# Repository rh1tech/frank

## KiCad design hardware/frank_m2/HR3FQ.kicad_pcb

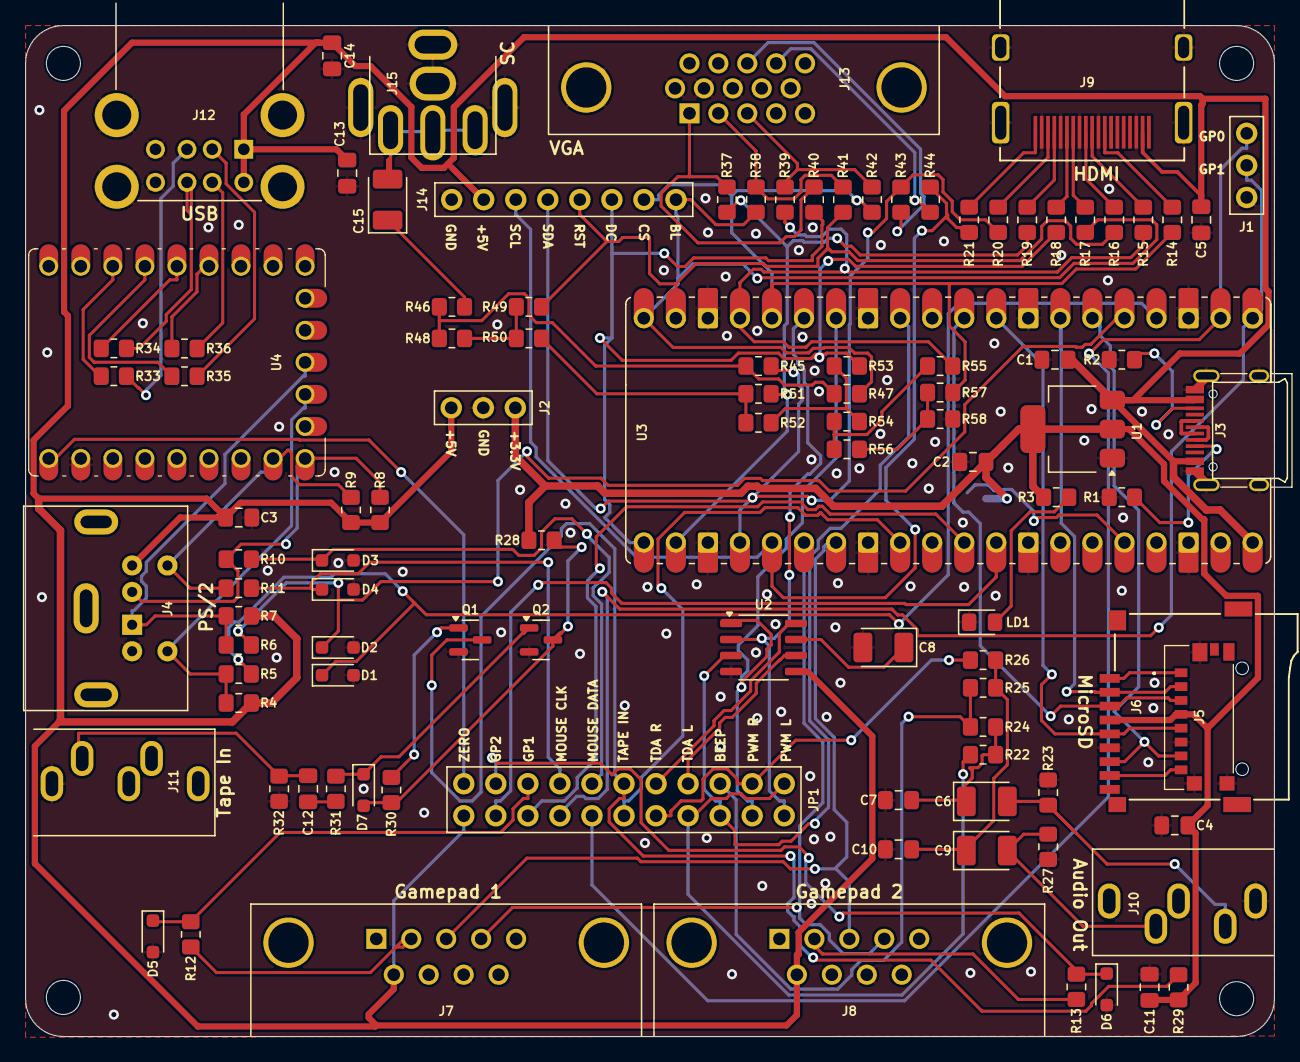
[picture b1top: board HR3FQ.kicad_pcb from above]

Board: 2 copper layers, 99.0 x 80.1 mm, 108 parts (1 on the bottom side), 91 nets.

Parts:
C1, C2, C13, C14: 10u; Capacitor (0805)
C3, C4, C5, C11, C12: 100n; Capacitor (0805)
C6, C8, C9: 10u; Capacitor (3528, tantalum, polar)
C7, C10: 10n; Capacitor (0805)
C15: 220u; Capacitor (3528, tantalum, polar)
D1, D2, D3, D4, D5, D6: 3V3; Diode (SOD-323)
D7: 1N4148; Diode (SOD-323)
H1, H2, H3, H4: Hole 2.7mm; Mounting Hole (2.7mm)
J1, J2: Pin Header 1x03; Pin Header (1x03)
J3: USB4215; USB Type C
J4: MDC-036; MiniDIN (6 Pin, female)
J5: 0475710001; MicroSD (SMD, short)
J6: 104031-0811; MicroSD (SMD, long)
J7, J8: D-SUB 9 Male; D-SUB (9 pin, male, top mount)
J9: DC3RX19JA2; HDMI (female)
J10, J11: SJ1-353XNG; Jack (3.5mm)
J12: SS-52100-004; USB Type A (stacked)
J13: D-SUB 15 Female; D-SUB (15 pin, female)
J14: Pin Header 1x08; Pin Header (1x08)
J15: RCA-103; RCA
JP1: Pin Header 2x18; Pin Header (2x11)
JP2: Jumper (Solder); Jumper (solder)
LD1: Green; LED (0805)
Q1, Q2: BC850; SOT-23
R1, R2: 5.1K; Resistor (0805)
R3, R4, R7, R8, R9, R12, R13, R22, R26, R29, R40, R41, R42: 1K; Resistor (0805)
R5, R6, R10, R11, R32, R43, R44: 100R; Resistor (0805)
R14, R15, R16, R17, R18, R19, R20, R21, R47, R49, R51, R53, R55, R57: 270R; Resistor (0805)
R23, R27, R37, R38, R39: 330R; Resistor (0805)
R24, R25: 2K; Resistor (0805)
R28, R30, R31: 10K; Resistor (0805)
R33, R34, R35, R36: 22R; Resistor (0805)
R45: 750R; Resistor (0805)
R46: 51R; Resistor (0805)
R48, R50, R52, R54, R56: 150R; Resistor (0805)
R58: 300R; Resistor (0805)
U1: NCP1117 3.3; SOT-223
U2: TDA1387T; SO-8
U3: Rasberry Pi Pico; Raspberry Pi Pico
U4: RP2040-Zero; Raspberry Pi Zero

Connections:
+3V3: C2.1, C4.2, C11.1, J2.1, J5.P4 (VDD), J6.4 (VDD), JP2.2 (B), R3.2, R28.1, R29.1, U1.2 (VO)
/A_OUTB: JP1.5, R24.2, R25.2
/A_OUTL: JP1.1, JP1.8, R22.2
/A_OUTR: JP1.3, JP1.10, R26.2
/A_TDAL: JP1.7, U2.6 (A_LEFT)
/A_TDAR: JP1.9, U2.8 (A_RIGHT)
/Audio Out/L: C6.2, J10.T, R23.1
/Audio Out/R: C9.2, J10.R, R27.1
/Composite/CVBS: C15.2, J15.1
/GP1_DATA: D5.1 (K), JP1.17, R12.1
/GP2_DATA: D6.1 (K), JP1.19, R13.1
/GPIO0: J1.2, JP1.16, U3.1 (GPIO0)
/GPIO1: J1.3, JP1.14, U3.2 (GPIO1)
/GPIO2: D1.1 (K), R5.2, U3.4 (GPIO2)
/GPIO3: D2.1 (K), R6.2, U3.5 (GPIO3)
/GPIO4: J5.P7 (DAT0), J6.7 (DAT0), U3.6 (GPIO4)
/GPIO5: J5.P2 (CD/DAT3), J6.2 (DAT3/CD), U3.7 (GPIO5)
/GPIO6: J5.P5 (CLK), J6.5 (CLK), U3.9 (GPIO6)
/GPIO7: J5.P3 (CMD), J6.3 (CMD), U3.10 (GPIO7)
/GPIO9: JP1.6, U2.3 (DATA), U3.12 (GPIO9)
/GPIO10: JP1.4, U2.1 (SCLK), U3.14 (GPIO10)
/GPIO11: JP1.2, U2.2 (LRCK), U3.15 (GPIO11)
/GPIO12: J14.7, R14.2, R42.1, R57.1, U3.16 (GPIO12)
/GPIO13: R15.2, R39.1, R55.1, U3.17 (GPIO13)
/GPIO14: J14.5, R16.2, R41.1, R49.1, U3.19 (GPIO14)
/GPIO15: J14.8, R17.2, R38.1, R47.1, U3.20 (GPIO15)
/GPIO16: J14.6, R18.2, R40.1, R53.1, U3.21 (GPIO16)
/GPIO17: R19.2, R37.1, R51.1, U3.22 (GPIO17)
/GPIO18: J14.4, R20.2, R43.2, R45.1, U3.24 (GPIO18)
/GPIO19: J14.3, R21.2, R44.2, U3.25 (GPIO19)
/GPIO20: J7.4, J8.4, U3.26 (GPIO20)
/GPIO21: J7.3, J8.3, U3.27 (GPIO21)
/GPIO22: JP1.12, U3.29 (GPIO22)
/GPIO26: JP1.18, U3.31 (GPIO26_ADC0)
/GPIO27: JP1.20, U3.32 (GPIO27_ADC1)
/KB_CLK: J4.5, R4.2, R5.1, U4.13 (12)
/KB_DATA: J4.1, R6.1, R7.2, U4.12 (11)
/LOAD_IN_D: JP1.11, Q1.3 (C), R29.2
/MS_CLK: J4.6, R9.2, R11.1, U4.16 (15)
/MS_CLK_3V: D4.1 (K), JP1.15, R11.2
/MS_DATA: J4.2, R8.2, R10.1, U4.15 (14)
/MS_DATA_3V: D3.1 (K), JP1.13, R10.2
/Micro SD/DAT1: J5.P8 (DAT1), J6.8 (DAT1)
/Micro SD/DAT2: J5.P1 (DAT2), J6.1 (DAT2)
/Power/D+: J3.6 (DP1), J3.8 (DP2)
/Power/D-: J3.5 (DN2), J3.7 (DN1)
/USB_D1M: R35.1, U4.4 (3)
/USB_D1P: R33.1, U4.3 (2)
/USB_D2M: R36.1, U4.6 (5)
/USB_D2P: R34.1, U4.5 (4)
/ZERO_VBUS: JP1.21, U4.23 (5V)
GND: C1.2, C2.2, C3.2, C4.1, C5.2, C7.2, C8.2, C10.2, C11.2, C13.2, C14.2, D1.2 (A), D2.2 (A), D3.2 (A), D4.2 (A), D5.2 (A), D6.2 (A), J1.1, J2.2, J3.1 (GND), J3.12 (GND), J3.13 (SHIELD), J4.3, J5.G1 (GND_1), J5.G2 (GND_2), J5.G3 (GND_3), J5.P6 (VSS), J6.6 (VSS), J7.8, J8.8, J9.2 (G_D2), J9.5 (G_D1), J9.8 (G_D0), J9.11 (G_CLK), J9.17 (G_DDC/CEC), J9.20 (SHIELD1), J9.21 (SHIELD2), J9.22 (SHIELD3), J9.23 (SHIELD4), J10.S, J11.S, J12.4 (GND1), J12.8 (GND2), J12.9 (Shield), J13.0, J13.5, J13.6, J13.7, J13.8, J13.10, J14.1, J15.2, LD1.1 (K), Q1.2 (E), Q2.2 (E), R1.1, R2.1, R23.2, R27.2, R32.2, R58.1, U1.1 (GND), U2.4 (AGND), U3.3 (GND), U3.8 (GND), U3.13 (GND), U3.18 (GND), U3.23 (GND), U3.28 (GND), U3.33 (AGND), U3.38 (GND), U4.22 (GND)
unnamed: C6.1, C7.1, R22.1, R24.1
unnamed: C9.1, C10.1, R25.1, R26.1
unnamed: C12.1, J11.T, R32.1
unnamed: C12.2, R31.1
unnamed: C15.1, R46.2
unnamed: D7.2 (A), Q2.3 (C), R28.2, R30.1
unnamed: D7.1 (K), Q2.1 (B), R31.2
unnamed: J3.4 (CC1), R1.2
unnamed: J3.10 (CC2), R2.2
unnamed: J7.2, R12.2
unnamed: J8.2, R13.2
unnamed: J9.12 (CLKN), R14.1
unnamed: J9.10 (CLKP), R15.1
unnamed: J9.9 (D0N), R16.1
unnamed: J9.7 (D0P), R17.1
unnamed: J9.6 (D1N), R18.1
unnamed: J9.4 (D1P), R19.1
unnamed: J9.3 (D2N), R20.1
unnamed: J9.1 (D2P), R21.1
unnamed: J12.3 (D1+), R33.2
unnamed: J12.2 (D1-), R35.2
unnamed: J12.7 (D2+), R34.2
unnamed: J12.6 (D2-), R36.2
unnamed: J13.1, R37.2, R40.2
unnamed: J13.2, R38.2, R41.2
unnamed: J13.3, R39.2, R42.2
unnamed: J13.13, R43.1
unnamed: J13.14, R44.1
unnamed: JP2.1 (A), U3.36 (3V3)
unnamed: LD1.2 (A), R3.1
unnamed: Q1.1 (B), R30.2
unnamed: R45.2, R46.1, R47.2, R48.2
unnamed: R48.1, R49.2, R50.2
unnamed: R50.1, R51.2, R52.2
unnamed: R52.1, R53.2, R54.2
unnamed: R54.1, R55.2, R56.2
unnamed: R56.1, R57.2, R58.2
unnamed: C8.1, U2.7 (FLT)
VBUS: C1.1, C3.1, C5.1, C13.1, C14.1, J2.3, J3.2 (VBUS), J3.11 (VBUS), J4.4, J7.6, J8.6, J9.18 (+5V), J12.1 (VBUS1), J12.5 (VBUS2), J14.2, JP1.22, R4.1, R7.1, R8.1, R9.1, U1.3 (VI), U2.5 (VA), U3.40 (VBUS)

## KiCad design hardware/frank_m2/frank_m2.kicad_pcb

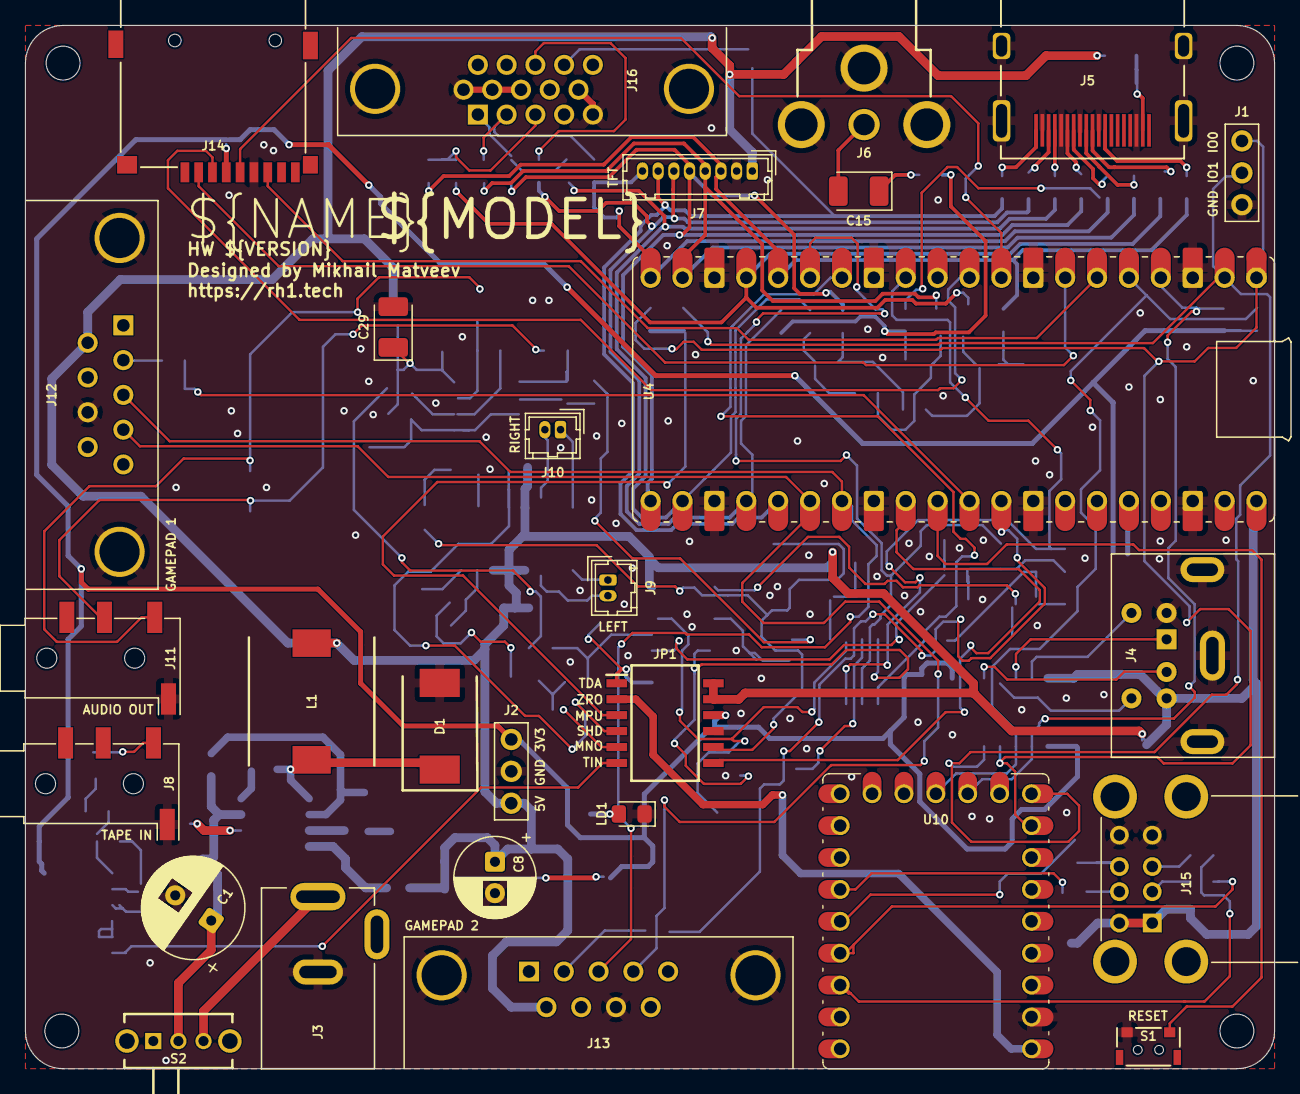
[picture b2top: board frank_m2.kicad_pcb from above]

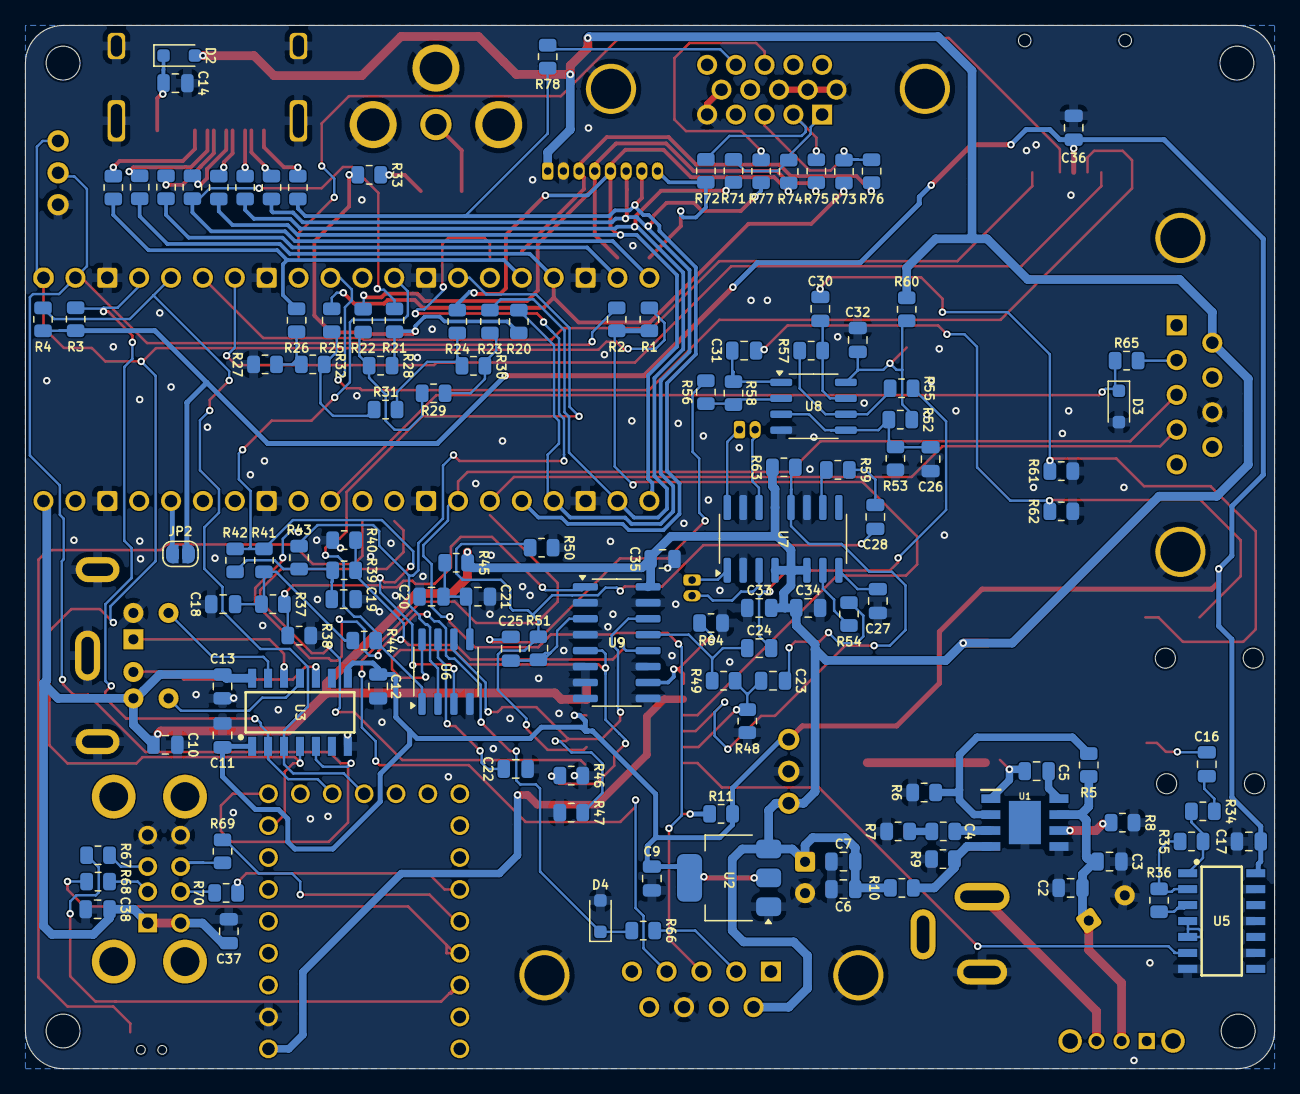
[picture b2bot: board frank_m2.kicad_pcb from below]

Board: 2 copper layers, 99.5 x 83.1 mm, 156 parts (124 on the bottom side), 117 nets.

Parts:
C1: 680u; C_Radial_D8.0mm_P3.50mm
C2, C7, C9, C20, C22, C24, C25, C26, C30, C31, C37, C38: 10u; C_0805_2012Metric
C3, C5, C6, C10, C11, C12, C13, C14, C16, C17, C21, C27, C32, C35, C36: 100n; C_0805_2012Metric
C4: 150pF; R_0805_2012Metric
C8: 220u; C_Radial_D6.3mm_P2.50mm
C15: 220u; C_3528_Tantalum
C18, C19: 47n; C_0805_2012Metric
C23, C28, C33: 1u; C_0805_2012Metric
C29: 10u; C_3528_Tantalum
C34: 47u; C_0805_2012Metric
D1: 1N5822; D_SMA_SS34
D2: 1N5819WS; D_SOD-323
D3, D4: 3V3; D_SOD-323
H1, H2, H3, H4: Hole 2.7mm; MountingHole_2.7mm
J1: UART; PinHeader_1x03_P2.54mm
J2: PWR; PinHeader_1x03_P2.54mm
J3: DC-005-5A-2.0; BarrelJack_DC-005
J4: MDC-036; MiniDIN_6pin_Female
J5: DC3RX19JA2; HDMI_Female
J6: RCA-103; BarrelJack_RCJ-012
J7: Pin Header 1x08; JST_GH_1x08_P1.25mm
J8, J11: PJ-320D; AudioJack_3.5mm_PJ320D
J9: PAM L; JST_GH_1x02_P1.25mm
J10: PAM R; JST_GH_1x02_P1.25mm
J12, J13: GP2; DSUB-9_Male_TopMount
J14: 104031-0811; MicroSD_SMD_Long
J15: SS-52100-004; USB_A_Stacked
J16: VGA; DSUB-15_Female
JP1: Config Switches; SOIC-12_P1.27mm
JP2: 3V3 Jumper; Jumper_Solder
L1: 22uH; Inductor_CDRH104RNP
LD1: Power; LED_0805
R1, R2, R3, R4, R37, R39, R49, R51, R52, R53, R54, R55, R56, R59, R63, R64: 10K; R_0805_2012Metric
R5, R7, R8, R35, R36: 100K; R_0805_2012Metric
R6: 24K; R_0805_2012Metric
R9: 8.2K; R_0805_2012Metric
R10: 43K; R_0805_2012Metric
R11, R43, R44, R65, R66, R74, R75, R76: 1K; R_0805_2012Metric
R12, R13, R14, R15, R16, R17, R18, R19, R21, R22, R23, R24, R25, R26: 270R; R_0805_2012Metric
R20: 750R; R_0805_2012Metric
R27: 300R; R_0805_2012Metric
R28, R29, R30, R31, R32: 150R; R_0805_2012Metric
R33: 51R; R_0805_2012Metric
R34: 4.7K; R_0805_2012Metric
R38, R40, R41, R42, R48, R50: 2K; R_0805_2012Metric
R45, R60, R77, R78: 100R; R_0805_2012Metric
R46, R47: 470R; R_0805_2012Metric
R57, R58: 47K; R_0805_2012Metric
R61, R62: 20K; R_0805_2012Metric
R67, R68, R69, R70: 22R; R_0805_2012Metric
R71, R72, R73: 330R; R_0805_2012Metric
S1: Reset; Button_SMD_TACT4623
S2: SK12D07VG3NS; Switch_Slide_SK12D07VG3NS
U1: MP1584EN-LF-Z; SOIC-9_P1.27mm
U2: AMS1117 3.3; SOT-223
U3: TXS0104EDR; SOIC-14_P1.27mm
U4: Rasberry Pi Pico 1/2; RaspberryPi_Pico
U5: CD4069UBM; SOIC-14_P1.27mm
U6: TDA1387T; SO-8
U7: PAM8403D; SOP-16_P1.27mm
U8: LM358; SO-8
U9: 74HC4052D; SOP-16_P1.27mm
U10: RP2040-Zero; RaspberryPi_Zero

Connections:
+3V3: C9.1, C11.1, C12.1, C17.1, C36.2, J2.1, J14.4 (VDD), JP1.10, JP2.2 (B), R3.2, R4.2, R11.2, U2.2 (VO), U3.1 (VCCA), U3.8 (OE), U5.14 (VDD)
/AMP_L: C24.1, R49.1, U9.13 (1Z)
/AMP_R: C25.1, R51.1, U9.3 (2Z)
/AUDIOSW: JP1.1, R64.2, U9.10 (S0)
/Audio/AMP_OUTL: C30.2, J11.T, R61.2
/Audio/AMP_OUTR: C31.2, J11.R, R62.2
/Audio/AMP_PAM_OUTL_M: J9.2, U7.3 (-OUTL)
/Audio/AMP_PAM_OUTL_P: J9.1, U7.1 (+OUT_L)
/Audio/AMP_PAM_OUTR_M: J10.2, U7.14 (-OUT_R)
/Audio/AMP_PAM_OUTR_P: J10.1, U7.16 (+OUT_R)
/Composite/CVBS: C15.2, J6.1
/LOAD_IN: JP1.6, U5.6 (I=*C)
/MONO_L: C23.1, JP1.5, R48.1, R49.2
/MONO_R: C28.1, JP1.8, R50.1, R51.2
/MSPUP3V3: JP1.3, R1.2, R2.2
/PGPIO0: J1.1, R1.1, U3.4 (A3), U4.1 (GPIO0), U10.16 (15)
/PGPIO1: J1.2, R2.1, U3.5 (A4), U4.2 (GPIO1), U10.15 (14)
/PGPIO2: R3.1, U3.2 (A1), U4.4 (GPIO2), U10.13 (12)
/PGPIO3: R4.1, U3.3 (A2), U4.5 (GPIO3), U10.12 (11)
/PGPIO4: J14.7 (DAT0), U4.6 (GPIO4)
/PGPIO5: J14.2 (DAT3/CD), U4.7 (GPIO5)
/PGPIO6: J14.5 (CLK), U4.9 (GPIO6)
/PGPIO7: J14.3 (CMD), U4.10 (GPIO7)
/PGPIO9: R41.1, R42.1, U4.12 (GPIO9), U6.3 (DATA)
/PGPIO10: R44.2, U4.14 (GPIO10), U6.1 (SCLK)
/PGPIO11: R43.2, U4.15 (GPIO11), U6.2 (LRCK)
/PGPIO12: J7.3, R14.2, R26.1, R76.1, U4.16 (GPIO12)
/PGPIO13: R18.2, R25.1, R73.1, U4.17 (GPIO13)
/PGPIO14: J7.4, R12.2, R22.1, R75.1, U4.19 (GPIO14)
/PGPIO15: J7.8, R15.2, R21.1, R72.1, U4.20 (GPIO15)
/PGPIO16: J7.5, R16.2, R24.1, R74.1, U4.21 (GPIO16)
/PGPIO17: R19.2, R23.1, R71.1, U4.22 (GPIO17)
/PGPIO18: J7.6, R13.2, R20.1, R77.2, U4.24 (GPIO18)
/PGPIO19: J7.7, R17.2, R78.2, U4.25 (GPIO19)
/PGPIO20: J12.4, J13.4, U4.26 (GPIO20)
/PGPIO21: J12.3, J13.3, U4.27 (GPIO21)
/PGPIO22: JP1.7, U4.29 (GPIO22)
/PGPIO26: D3.1 (K), R65.1, U4.31 (GPIO26_ADC0)
/PGPIO27: D4.1 (K), R66.1, U4.32 (GPIO27_ADC1)
/PRUN: S1.1, U4.30 (RUN)
/PS2/KB_CLK_5V: J4.5, U3.13 (B1)
/PS2/KB_DATA_5V: J4.1, U3.12 (B2)
/PS2/MS_CLK_5V: J4.6, U3.11 (B3)
/PS2/MS_DATA_5V: J4.2, U3.10 (B4)
/PWM_L: R39.2, R40.1, U9.12 (1Y0)
/PWM_R: R37.2, R38.1, U9.1 (2Y0)
/Power/EN: R5.1, R6.1, U1.2 (EN)
/Power/VBUS_IN: C1.1, C2.1, C3.1, R5.2, S2.2, U1.7 (VIN)
/SHND: JP1.4, R63.2, U7.12 (SHND)
/TDA_L: R47.2, U6.6 (A_LEFT), U9.14 (1Y1)
/TDA_R: R46.1, U6.8 (A_RIGHT), U9.5 (2Y1)
/Tape In/TAPE: C16.2, J8.T
/ZGPIO2: R67.1, U10.3 (2)
/ZGPIO3: R68.1, U10.4 (3)
/ZGPIO4: R69.1, U10.5 (4)
/ZGPIO5: R70.1, U10.6 (5)
/Z_VBUS: JP1.2, U10.23 (5V)
GND: C1.2, C2.2, C3.2, C6.1, C7.2, C8.2, C9.2, C10.2, C11.2, C12.2, C13.2, C14.2, C17.2, C18.2, C19.2, C20.2, C21.2, C22.2, C26.1, C27.2, C29.2, C32.1, C33.2, C34.2, C35.1, C36.1, C37.2, C38.2, D1.2 (A), D3.2 (A), D4.2 (A), J1.3, J2.2, J3.2, J4.3, J5.2 (G_D2), J5.5 (G_D1), J5.8 (G_D0), J5.11 (G_CLK), J5.17 (G_DDC/CEC), J5.20 (SHIELD1), J5.21 (SHIELD2), J5.22 (SHIELD3), J5.23 (SHIELD4), J6.2, J7.2, J8.S, J11.S, J12.8, J13.8, J14.6 (VSS), J15.4 (GND1), J15.8 (GND2), J16.0, J16.5, J16.6, J16.7, J16.8, J16.10, JP1.9, LD1.1 (K), R6.2, R7.2, R8.2, R9.1, R27.1, R38.2, R40.2, R46.2, R47.1, R48.2, R50.2, R53.1, R61.1, R62.1, R64.1, S1.2, U1.5 (GND), U1.9 (EP), U2.1 (GND), U3.7 (GND), U4.3 (GND), U4.8 (GND), U4.13 (GND), U4.18 (GND), U4.23 (GND), U4.28 (GND), U4.33 (AGND), U4.38 (GND), U5.7 (VSS), U5.9 (D14), U5.11 (E), U5.13 (F), U6.4 (AGND), U7.2 (PGND), U7.11 (GND), U7.15 (PGND), U8.4 (V-), U9.2 (2Y2), U9.4 (2Y3), U9.6 (~E), U9.7 (VEE), U9.8 (GND), U9.9 (S1), U9.11 (1Y3), U9.15 (1Y2), U10.22 (GND)
unnamed: C4.2, R7.1
unnamed: C15.1, R33.2
unnamed: C16.1, R34.2
unnamed: C18.1, R37.1, R41.2, R44.1
unnamed: C19.1, R39.1, R42.2, R43.1
unnamed: C23.2, R54.2
unnamed: C24.2, R55.2
unnamed: C25.2, R56.2
unnamed: C28.2, R59.2
unnamed: C30.1, R57.1, U8.7
unnamed: C31.1, R58.1, U8.1
unnamed: C5.2, D1.1 (K), L1.1, U1.1 (SW)
unnamed: C14.1, D2.1 (K), J5.18 (+5V)
unnamed: J3.1, S2.3
unnamed: J5.12 (CLKN), R14.1
unnamed: J5.10 (CLKP), R18.1
unnamed: J5.9 (D0N), R12.1
unnamed: J5.7 (D0P), R15.1
unnamed: J5.6 (D1N), R16.1
unnamed: J5.4 (D1P), R19.1
unnamed: J5.3 (D2N), R13.1
unnamed: J5.1 (D2P), R17.1
unnamed: J12.2, R65.2
unnamed: J13.2, R66.2
unnamed: J15.3 (D1+), R67.2
unnamed: J15.2 (D1-), R68.2
unnamed: J15.7 (D2+), R69.2
unnamed: J15.6 (D2-), R70.2
unnamed: J16.1, R71.2, R74.2
unnamed: J16.2, R72.2, R75.2
unnamed: J16.3, R73.2, R76.2
unnamed: J16.13, R77.1
unnamed: J16.14, R78.1
unnamed: JP2.1 (A), U4.36 (3V3)
unnamed: LD1.2 (A), R11.1
unnamed: R20.2, R21.2, R28.2, R33.1
unnamed: R22.2, R28.1, R29.2
unnamed: R23.2, R29.1, R30.2
unnamed: R24.2, R30.1, R31.2
unnamed: R25.2, R31.1, R32.2
unnamed: R26.2, R27.2, R32.1
unnamed: C5.1, U1.8 (BST)
unnamed: C4.1, U1.3 (COMP)
unnamed: R9.2, R10.2, U1.4 (FB)
unnamed: R8.1, U1.6 (FREQ)
unnamed: R34.1, R35.2, U5.1 (A)
unnamed: R36.1, U5.3 (B)
unnamed: U5.4 (H=*B), U5.5 (C)
unnamed: R35.1, R36.2, U5.2 (G-*A)
unnamed: C22.1, U6.7 (FLT)
unnamed: C20.1, C21.1, R45.1, U6.5 (VA)
unnamed: R54.1, U7.7 (INL)
unnamed: R59.1, U7.10 (INR)
unnamed: C27.1, U7.8 (VREF)
unnamed: C26.2, R52.1, R53.2, U8.3 (+), U8.5 (+)
unnamed: R56.1, R58.2, U8.2 (-)
unnamed: R55.1, R57.2, U8.6 (-)
unnamed: C29.1, C32.2, R52.2, R60.2, U8.8 (V+)
VBUS: C6.2, C7.1, C8.1, C10.1, C13.1, C33.1, C34.1, C35.2, C37.1, C38.1, D2.2 (A), J2.3, J4.4, J7.1, J12.6, J13.6, J15.1 (VBUS1), J15.5 (VBUS2), JP1.11, JP1.12, L1.2, R10.1, R45.2, R60.1, R63.1, U2.3 (VI), U3.14 (VCCB), U4.40 (VBUS), U7.4 (PVDD), U7.5 (MUTE), U7.6 (VDD), U7.13 (PVDD), U9.16 (VCC)

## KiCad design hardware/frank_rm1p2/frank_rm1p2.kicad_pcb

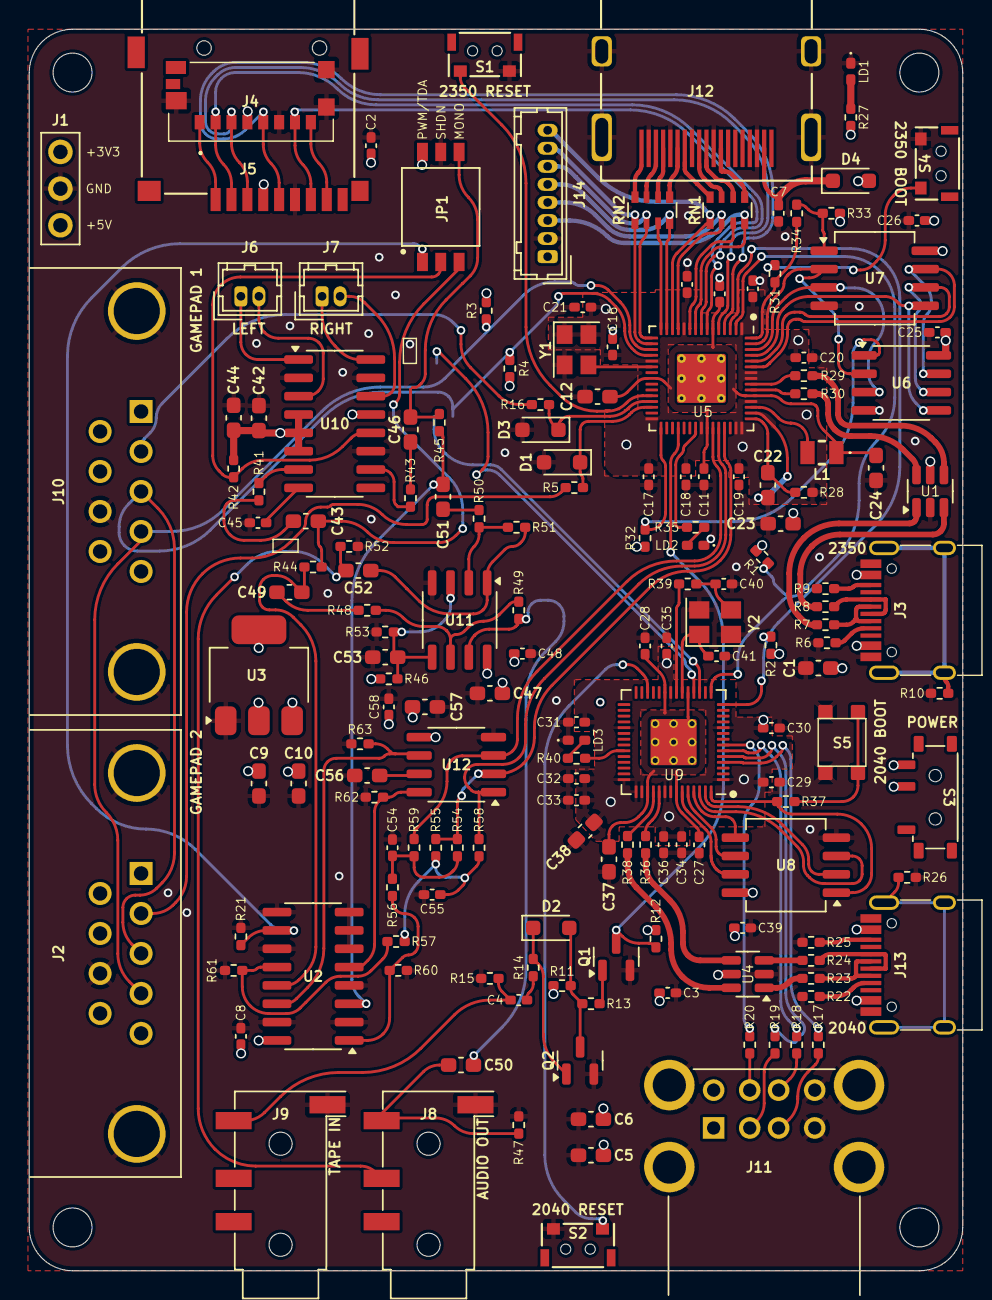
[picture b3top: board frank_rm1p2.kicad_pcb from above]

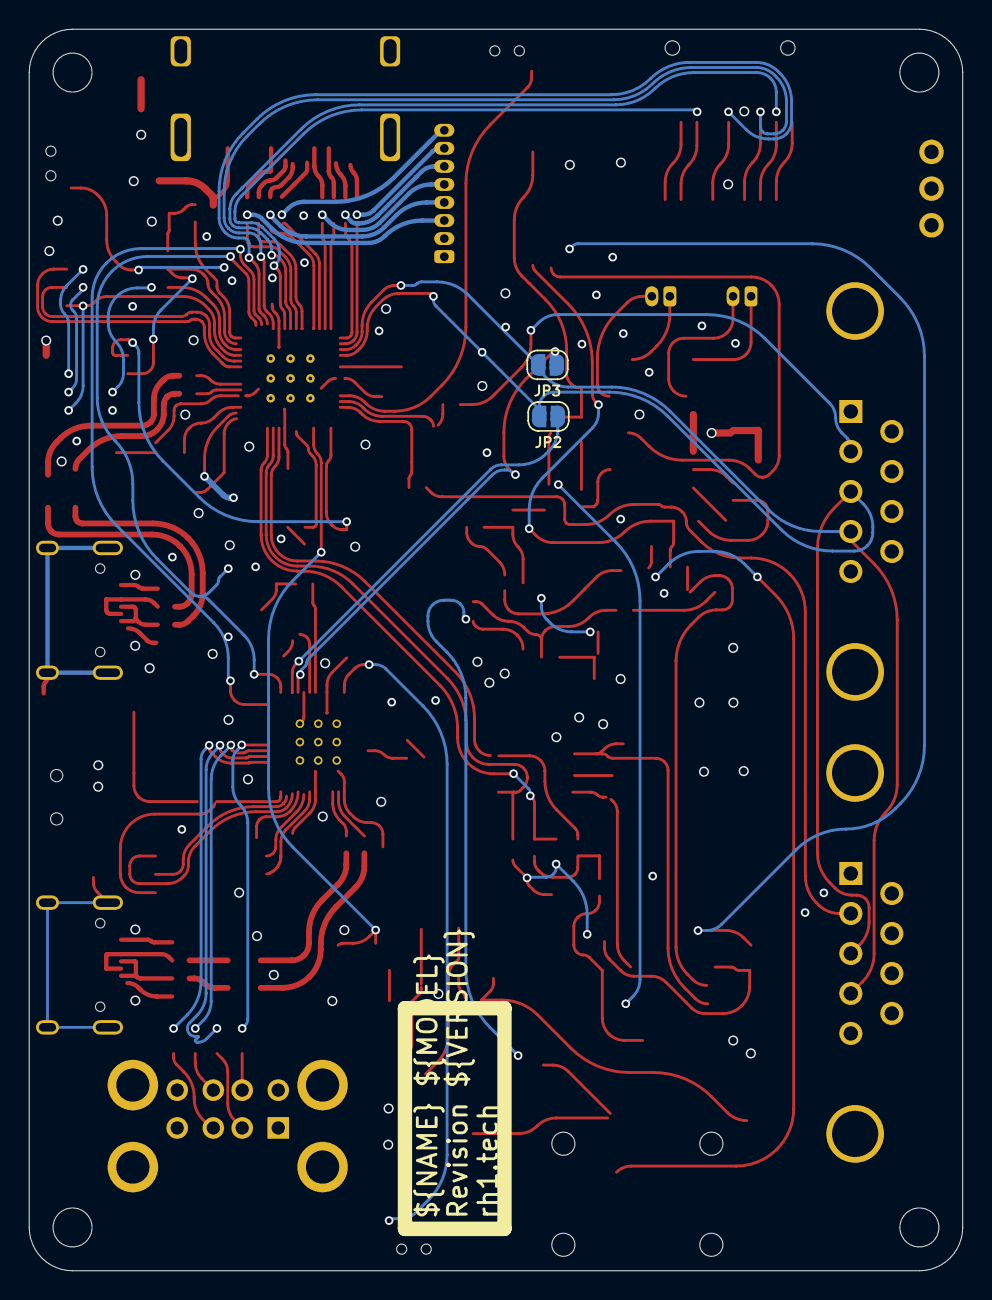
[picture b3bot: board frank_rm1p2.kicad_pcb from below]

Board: 4 copper layers, 64.7 x 86.0 mm, 173 parts (2 on the bottom side), 138 nets.

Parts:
C1, C5, C6, C9, C10, C47, C49, C50, C51, C52, C53, C56, C57: 10u; Capacitor (0603)
C2, C3, C4, C7, C8, C11, C13, C14, C15, C16, C17, C18, C19, C20, C21, C25, C26, C27, C28, C29, C30, C31, C32, C33, C34, C35, C36, C39, C45, C48, C58: 100n; Capacitor (0402)
C12, C22, C23, C24: 4.7u; Capacitor (0603)
C37, C38, C42, C43, C46: 1u; Capacitor (0603)
C40, C41: 15p; Capacitor (0402)
C44: 47u; Capacitor (0603)
C54, C55: 47n; Capacitor (0402)
D1, D3: 3V3; Diode (SOD-323)
D2: 1N4148; Diode (SOD-323)
D4: 1N5819WS; Diode (SOD-323)
H1, H2, H3, H4: MountingHole; Mounting Hole (2.7mm)
J1: PWR; Pin Header (1x03)
J2, J10: D-SUB 9 Male; D-SUB (9 pin, male, top mount)
J3, J13: USB4215-03-A; USB Type C
J4: 0475710001; MicroSD (SMD, short)
J5: 104031-0811; MicroSD (SMD, long)
J6: PAM L; Connector Female 1.25 JST 2P
J7: PAM R; Connector Female 1.25 JST 2P
J8, J9: PJ-320D; Jack (3.5mm, PJ-320D)
J11: SS-52100-004; USB Type A (stacked)
J12: DC3RX19JA2; HDMI (female)
J14: Pin Header 1x08; Connector Female 1.25 JST 8P
JP1: Main Jumpers; SW_DS05-127-2-03BK-SMT-TR
JP2: Mouse (DATA); Jumper (solder)
JP3: Mouse (CLK); Jumper (solder)
L1: 3.3u; Inductor (0806)
LD1: Power; LED (0402)
LD2, LD3: Blue; LED (0402)
Q1, Q2: BC850; SOT-23
R1, R2, R3, R4, R11, R13, R14, R21, R32, R33, R41, R42, R43, R44, R45, R46, R48, R50, R53, R56, R57: 10K; Resistor (0402)
R5, R12, R16, R27, R31, R35, R37, R39, R40, R58, R59: 1K; Resistor (0402)
R6, R9, R22, R25: 5.1K; Resistor (0402)
R7, R8, R17, R18, R19, R20, R23, R24: 22R; Resistor (0402)
R10, R26: 1M; Resistor (0402)
R15: 100R; Resistor (0402)
R28: 33R; Resistor (0402)
R29, R30, R36, R38: 27R; Resistor (0402)
R34: 0R; Resistor (0402)
R47, R52: 20K; Resistor (0402)
R49, R51: 47K; Resistor (0402)
R54, R55, R60, R61: 2K; Resistor (0402)
R62, R63: 470R; Resistor (0402)
RN1, RN2: 270R; Resistor Array (4x0603)
S1: Reset RP2530A; TACT-SIDE-4623
S2: Reset RP2040; TACT-SIDE-4623
S3: MSK12C02; Switch (MSK12C02)
S4: Boot 2350; TACT-SIDE-4623
S5: Boot 2040; Button (SMD, 3x3mm, 1-1)
U1, U4: USBLC6-2SC6; SOT-23-6
U2: 74HC4052D; SOP-16
U3: NCP1117 3.3; SOT-223
U5: RP2350; QFN 60 (RP2350A)
U6: ESP-PSRAM32; SO-8
U7: W25Q128JVS; SOIC-8
U8: W25Q128JVSIQ; SOIC-8
U9: RP2040; QFN 56
U10: PAM8403D; SOP-16
U11: LM358; SO-8
U12: TDA1387T; SO-8
Y1: ASE-12MHz; Crystal (3225, active)
Y2: 12 MHz; Crystal (3225)

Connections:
+1V1: C11.1, C12.1, C13.1, C24.1, L1.1, U5.6 (DVDD), U5.23 (DVDD), U5.39 (DVDD), U5.50 (VREG_FB)
+3V3: C2.2, C3.1, C8.2, C9.1, C14.1, C15.1, C16.1, C17.1, C18.1, C19.1, C20.1, C21.1, C23.1, C25.1, C26.1, C29.1, C30.1, C31.1, C32.1, C33.1, C34.1, C35.1, C36.1, C38.1, C39.1, J1.1, J4.P4 (VDD), J5.4 (VDD), R1.2, R2.2, R3.2, R4.2, R11.1, R12.1, R27.2, R28.1, R32.2, R33.1, U2.16 (VCC), U3.2 (VO), U5.1 (IOVDD), U5.11 (IOVDD), U5.20 (IOVDD), U5.30 (IOVDD), U5.38 (IOVDD), U5.44 (ADC_AVDD), U5.45 (IOVDD), U5.49 (VREG_VIN), U5.53 (USB_OTP_VDD), U5.54 (QSPI_IOVDD), U6.8 (VCC), U7.8 (VCC), U8.8 (VCC), U9.1 (IOVDD), U9.10 (IOVDD), U9.22 (IOVDD), U9.33 (IOVDD), U9.42 (IOVDD), U9.43 (ADC_AVDD), U9.44 (VREG_IN), U9.48 (USB_VDD), U9.49 (IOVDD), Y1.1 (EN), Y1.4 (Vdd)
/AMP_IN_L: C49.1, R44.1, U2.13 (1Z)
/AMP_IN_R: C51.1, R45.1, U2.3 (2Z)
/AUDIOSW: JP1.1, R21.2, U2.10 (S0)
/Audio Out/AMP_OUTL: C50.2, J8.T, R47.2
/Audio Out/AMP_OUTR: C52.2, J8.R, R52.2
/Audio Out/AMP_PAM_OUTL_M: J6.2, U10.3 (-OUTL)
/Audio Out/AMP_PAM_OUTL_P: J6.1, U10.1 (+OUT_L)
/Audio Out/AMP_PAM_OUTR_M: J7.2, U10.14 (-OUT_R)
/Audio Out/AMP_PAM_OUTR_P: J7.1, U10.16 (+OUT_R)
/D+: R29.1, U1.4 (I/O2)
/D-: R30.1, U1.6 (I/O1)
/DAT1: J4.P8 (DAT1), J5.8 (DAT1)
/DAT2: J4.P1 (DAT2), J5.1 (DAT2)
/GPIO0: R1.1, U5.2 (GPIO0), U9.15 (GPIO12)
/GPIO1: R2.1, U5.3 (GPIO1), U9.14 (GPIO11)
/GPIO2: J4.P5 (CLK), J5.5 (CLK), U5.4 (GPIO2)
/GPIO3: J4.P3 (CMD), J5.3 (CMD), U5.5 (GPIO3)
/GPIO4: J4.P7 (DAT0), J5.7 (DAT0), U5.7 (GPIO4)
/GPIO5: J4.P2 (CD/DAT3), J5.2 (DAT3/CD), U5.8 (GPIO5)
/GPIO6: J14.3, RN1.4 (R4.1), U5.9 (GPIO6)
/GPIO7: RN1.3 (R3.1), U5.10 (GPIO7)
/GPIO8: J14.4, RN1.2 (R2.1), U5.12 (GPIO8)
/GPIO9: J14.8, RN1.1 (R1.1), U5.13 (GPIO9)
/GPIO10: J14.5, RN2.4 (R4.1), U5.14 (GPIO10)
/GPIO11: RN2.3 (R3.1), U5.15 (GPIO11)
/GPIO12: J14.6, RN2.2 (R2.1), U5.16 (GPIO12)
/GPIO13: J14.7, RN2.1 (R1.1), U5.17 (GPIO13)
/GPIO14: J2.4, J10.4, JP3.2 (B), R3.1, U5.18 (GPIO14)
/GPIO15: J2.3, J10.3, JP2.2 (B), R4.1, U5.19 (GPIO15)
/GPIO16: D3.1 (K), R16.1, U5.27 (GPIO16)
/GPIO17: D1.1 (K), R5.1, U5.28 (GPIO17)
/GPIO19: R32.1, U5.31 (GPIO19), U6.1 (~CE)
/GPIO22: Q1.3 (C), R12.2, U5.34 (GPIO22)
/GPIO26: R59.2, U5.40 (GPIO26_ADC0), U12.3 (DATA)
/GPIO27: R58.2, U5.41 (GPIO27_ADC1), U12.1 (SCLK)
/GPIO28: R54.1, R55.1, U5.42 (GPIO28_ADC2), U12.2 (LRCK)
/MONO_L: C43.1, JP1.3, R44.2
/MONO_R: C46.1, JP1.4, R45.2
/MS_CLK: JP3.1 (A), U9.18 (GPIO15)
/MS_DATA: JP2.1 (A), U9.17 (GPIO14)
/PWM_OUT_L: R57.2, R61.1, U2.12 (1Y0)
/PWM_OUT_R: R56.2, R60.1, U2.1 (2Y0)
/RP2_D+: R36.1, U4.4 (I/O2)
/RP2_D-: R38.1, U4.6 (I/O1)
/RP2_GPIO2: R17.1, U9.4 (GPIO2)
/RP2_GPIO3: R19.1, U9.5 (GPIO3)
/RP2_GPIO4: R18.1, U9.6 (GPIO4)
/RP2_GPIO5: R20.1, U9.7 (GPIO5)
/RP2_RUN: S2.1, U9.26 (RUN)
/RP2040/GPIO25: R40.2, U9.37 (GPIO25)
/RP2040/QSPI_SCLK: U8.6 (CLK), U9.52 (QSPI_SCLK)
/RP2040/QSPI_SD0: U8.5 (DI(IO0)), U9.53 (QSPI_SD0)
/RP2040/QSPI_SD1: U8.2 (DO(IO1)), U9.55 (QSPI_SD1)
/RP2040/QSPI_SD2: U8.3 (IO2), U9.54 (QSPI_SD2)
/RP2040/QSPI_SD3: U8.7 (IO3), U9.51 (QSPI_SD3)
/RP2040/QSPI_SS: R37.1, U8.1 (~CS), U9.56 (QSPI_SS)
/RP2040/XIN: C41.1, U9.20 (XIN), Y2.1
/RP2040/XOUT: R39.1, U9.21 (XOUT)
/RP2350A/FLASH_SS: R33.2, R34.2, U7.1 (~CS)
/RP2350A/QSPI_SCLK: U5.56 (QSPI_SCLK), U6.6 (SCLK), U7.6 (CLK)
/RP2350A/QSPI_SD0: U5.57 (QSPI_SD0), U6.5 (SI/SIO), U7.5 (DI(IO0))
/RP2350A/QSPI_SD1: U5.59 (QSPI_SD1), U6.2 (SO/SIO), U7.2 (DO(IO1))
/RP2350A/QSPI_SD2: U5.58 (QSPI_SD2), U6.3 (SIO2), U7.3 (IO2)
/RP2350A/QSPI_SD3: U5.55 (QSPI_SD3), U6.7 (SIO3), U7.7 (IO3)
/RP2350A/QSPI_SS: R31.1, R34.1, U5.60 (QSPI_SS)
/RP2350A/VREG_AVDD: C22.1, R28.2, U5.46 (VREG_AVDD)
/RP2350A/VREG_LX: L1.2, U5.48 (VREG_LX)
/RP2350A/XIN: U5.21 (XIN), Y1.3 (OUT)
/RP2350A/~USB_BOOT: R31.2, S4.2
/RUN: S1.1, U5.26 (RUN)
/SHND: JP1.2, R42.2, U10.12 (SHND)
/TDA_L: R63.2, U2.14 (1Y1), U12.6 (A_LEFT)
/TDA_R: R62.1, U2.5 (2Y1), U12.8 (A_RIGHT)
GND: C1.2, C2.1, C3.2, C5.2, C6.2, C7.2, C8.1, C9.2, C10.2, C11.2, C12.2, C13.2, C14.2, C15.2, C16.2, C17.2, C18.2, C19.2, C20.2, C21.2, C22.2, C23.2, C24.2, C25.2, C26.2, C27.2, C28.2, C29.2, C30.2, C31.2, C32.2, C33.2, C34.2, C35.2, C36.2, C37.2, C38.2, C39.2, C40.2, C41.2, C42.2, C44.2, C45.2, C47.1, C48.1, C53.1, C54.2, C55.2, C56.2, C57.2, C58.2, D1.2 (A), D3.2 (A), J1.2, J2.8, J3.1 (GND), J3.12 (GND), J4.G1 (GND_1), J4.G2 (GND_2), J4.G3 (GND_3), J4.P6 (VSS), J5.6 (VSS), J8.S, J9.S, J10.8, J11.4 (GND1), J11.8 (GND2), J11.9 (Shield), J12.2 (G_D2), J12.5 (G_D1), J12.8 (G_D0), J12.11 (G_CLK), J12.17 (G_DDC/CEC), J12.20 (SHIELD1), J12.21 (SHIELD2), J12.22 (SHIELD3), J12.23 (SHIELD4), J13.1 (GND), J13.12 (GND), J14.2, JP1.5, LD1.1 (K), LD2.1 (K), LD3.1 (K), Q1.2 (E), Q2.2 (E), R6.1, R9.1, R10.2, R15.2, R21.1, R22.1, R25.1, R26.2, R47.1, R52.1, R53.1, R60.2, R61.2, R62.2, R63.1, S1.2, S2.2, S4.1, S5.2, U1.2 (GND), U2.2 (2Y2), U2.4 (2Y3), U2.6 (~E), U2.7 (VEE), U2.8 (GND), U2.9 (S1), U2.11 (1Y3), U2.15 (1Y2), U3.1 (GND), U4.2 (GND), U5.47 (VREG_PGND), U5.61 (GND), U6.4 (VSS), U7.4 (GND), U8.4 (GND), U9.19 (TESTEN), U9.57 (GND), U10.2 (PGND), U10.11 (GND), U10.15 (PGND), U11.4 (V-), U12.4 (AGND), Y1.2 (GND), Y2.2, Y2.4
GPIO25: R35.2, U5.37 (GPIO25)
unnamed: C4.1, J9.T, R15.1
unnamed: C4.2, R14.1
unnamed: C40.1, R39.2, Y2.3
unnamed: C43.2, R41.2
unnamed: C46.2, R43.2
unnamed: C49.2, R48.2
unnamed: C50.1, R49.1, U11.7
unnamed: C51.2, R50.2
unnamed: C52.1, R51.1, U11.1
unnamed: C54.1, R54.2, R56.1, R59.1
unnamed: C55.1, R55.2, R57.1, R58.1
unnamed: D2.2 (A), Q2.3 (C), R11.2, R13.1
unnamed: D2.1 (K), Q2.1 (B), R14.2
unnamed: C7.1, D4.1 (K), J12.18 (+5V)
unnamed: J2.2, R5.2
unnamed: J3.4 (CC1), R6.2
unnamed: J3.10 (CC2), R9.2
unnamed: J3.5 (DN2), J3.7 (DN1), R7.2
unnamed: J3.6 (DP1), J3.8 (DP2), R8.2
unnamed: J3.13 (SHIELD), R10.1
unnamed: J10.2, R16.2
unnamed: J11.3 (D1+), R17.2
unnamed: J11.2 (D1-), R19.2
unnamed: J11.7 (D2+), R18.2
unnamed: J11.6 (D2-), R20.2
unnamed: J12.12 (CLKN), RN1.5 (R4.2)
unnamed: J12.10 (CLKP), RN1.6 (R3.2)
unnamed: J12.9 (D0N), RN1.7 (R2.2)
unnamed: J12.7 (D0P), RN1.8 (R1.2)
unnamed: J12.6 (D1N), RN2.5 (R4.2)
unnamed: J12.4 (D1P), RN2.6 (R3.2)
unnamed: J12.3 (D2N), RN2.7 (R2.2)
unnamed: J12.1 (D2P), RN2.8 (R1.2)
unnamed: J13.4 (CC1), R22.2
unnamed: J13.10 (CC2), R25.2
unnamed: J13.5 (DN2), J13.7 (DN1), R23.2
unnamed: J13.6 (DP1), J13.8 (DP2), R24.2
unnamed: J13.13 (SHIELD), R26.1
unnamed: LD1.2 (A), R27.1
unnamed: LD2.2 (A), R35.1
unnamed: LD3.2 (A), R40.1
unnamed: Q1.1 (B), R13.2
unnamed: R7.1, U1.1 (I/O1)
unnamed: R8.1, U1.3 (I/O2)
unnamed: R23.1, U4.1 (I/O1)
unnamed: R24.1, U4.3 (I/O2)
unnamed: R37.2, S5.1
unnamed: J13.2 (VBUS), J13.11 (VBUS), S3.2 (B)
unnamed: R30.2, U5.51 (USB_DM)
unnamed: R29.2, U5.52 (USB_DP)
unnamed: R38.2, U9.46 (USB_DM)
unnamed: R36.2, U9.47 (USB_DP)
unnamed: C27.1, C28.1, C37.1, U9.23 (DVDD), U9.45 (VREG_VOUT), U9.50 (DVDD)
unnamed: R41.1, U10.7 (INL)
unnamed: R43.1, U10.10 (INR)
unnamed: C45.1, U10.8 (VREF)
unnamed: C53.2, R46.1, R53.2, U11.3 (+), U11.5 (+)
unnamed: R50.1, R51.2, U11.2 (-)
unnamed: R48.1, R49.2, U11.6 (-)
unnamed: C56.1, U12.7 (FLT)
VBUS: C1.1, C5.1, C6.1, C10.1, C42.1, C44.1, C47.2, C48.2, C57.1, C58.1, D4.2 (A), J1.3, J2.6, J3.2 (VBUS), J3.11 (VBUS), J10.6, J11.1 (VBUS1), J11.5 (VBUS2), J14.1, JP1.6, R42.1, R46.2, S3.3 (A), U1.5 (VBUS), U3.3 (VI), U4.5 (VBUS), U10.4 (PVDD), U10.5 (MUTE), U10.6 (VDD), U10.13 (PVDD), U11.8 (V+), U12.5 (VA)

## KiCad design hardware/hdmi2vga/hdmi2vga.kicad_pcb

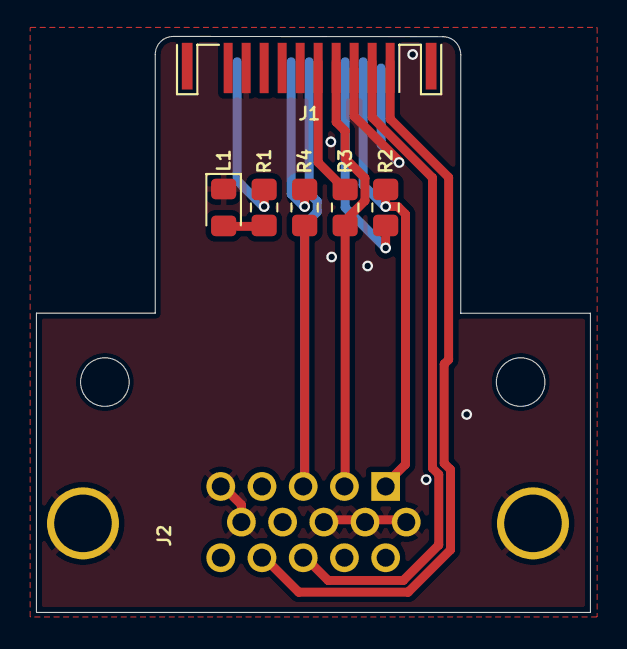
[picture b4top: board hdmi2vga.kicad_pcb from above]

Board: 2 copper layers, 30.8 x 32.0 mm, 9 parts (0 on the bottom side), 11 nets.

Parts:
H1, H2: MountingHole; Mounting Hole (2.7mm)
J1: HDMI; HDMI (male)
J2: VGA; D-SUB (15 pin, female)
L1: HDMI LED; LED (0805)
R1: 1K; Resistor (0805)
R2, R3, R4: 820R; Resistor (0805)

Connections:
/CLKN_VGA_B: J1.12 (CLKN), R4.1
/CLKP_VGA_BH: J1.10 (CLKP), J2.3, R4.2
/D0N_VGA_G: J1.9 (D0N), R3.1
/D0P_VGA_GH: J1.7 (D0P), J2.2, R3.2
/D1N_VGA_R: J1.6 (D1N), R2.1
/D1P_VGA_RH: J1.4 (D1P), J2.1, R2.2
/D2N_VGA_HS: J1.3 (D2N), J2.13
/D2P_VGA_VS: J1.1 (D2P), J2.14
GND: J1.2 (G_D2), J1.5 (G_D1), J1.8 (G_D0), J1.11 (G_CLK), J1.17 (G_DDC/CEC), J2.0, J2.5, J2.6, J2.7, J2.8, J2.10, L1.1 (K)
unnamed: J1.18 (+5V), R1.1
unnamed: L1.2 (A), R1.2
